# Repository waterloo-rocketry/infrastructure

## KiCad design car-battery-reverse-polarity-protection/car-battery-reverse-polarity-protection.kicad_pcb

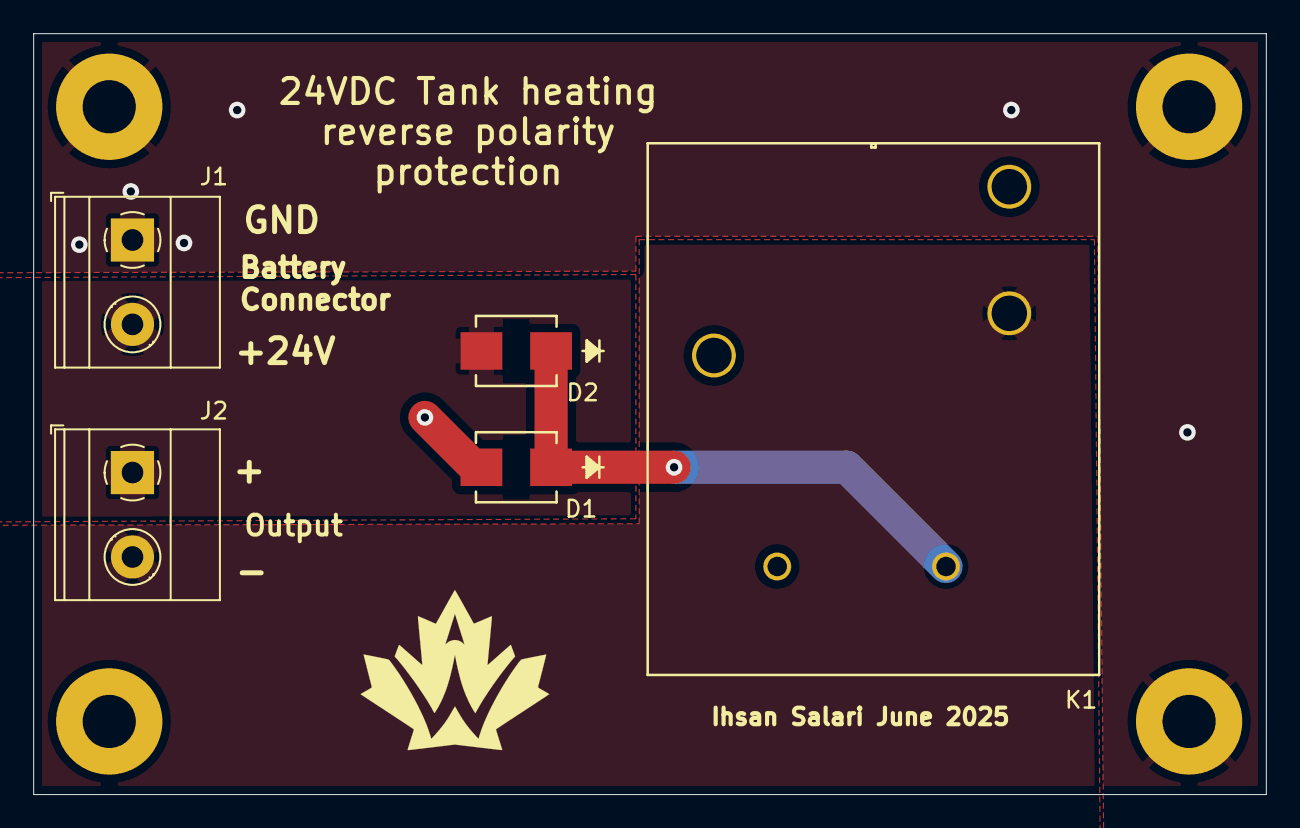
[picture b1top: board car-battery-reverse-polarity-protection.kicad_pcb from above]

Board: 2 copper layers, 74.2 x 45.8 mm, 10 parts (1 on the bottom side), 4 nets.

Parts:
D1, D2: STPS2L25U; SMB_STM-M
H1, H2, H3, H5: MountingHole_Pad; MountingHole_3.2mm_M3_Pad
H4: Logo; rocketry_logo_small_noletters
J1: Battery Connector; TerminalBlock_Phoenix_MKDS-1,5-2-5.08_1x02_P5.08mm_Horizont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
J2: Output; TerminalBlock_Phoenix_MKDS-1,5-2-5.08_1x02_P5.08mm_Horizont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
K1: AZ2150-1AE-24DEF; AZ2150_AMZ

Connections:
+BATT: D2.2 (A), J1.2, J2.1
/relay_coil: D1.1 (K), D2.1 (K), K1.A1
/relay_load_terminal: J2.2, K1.14
GND: D1.2 (A), H1.1, H2.1, H3.1, H5.1, J1.1, K1.13, K1.A2

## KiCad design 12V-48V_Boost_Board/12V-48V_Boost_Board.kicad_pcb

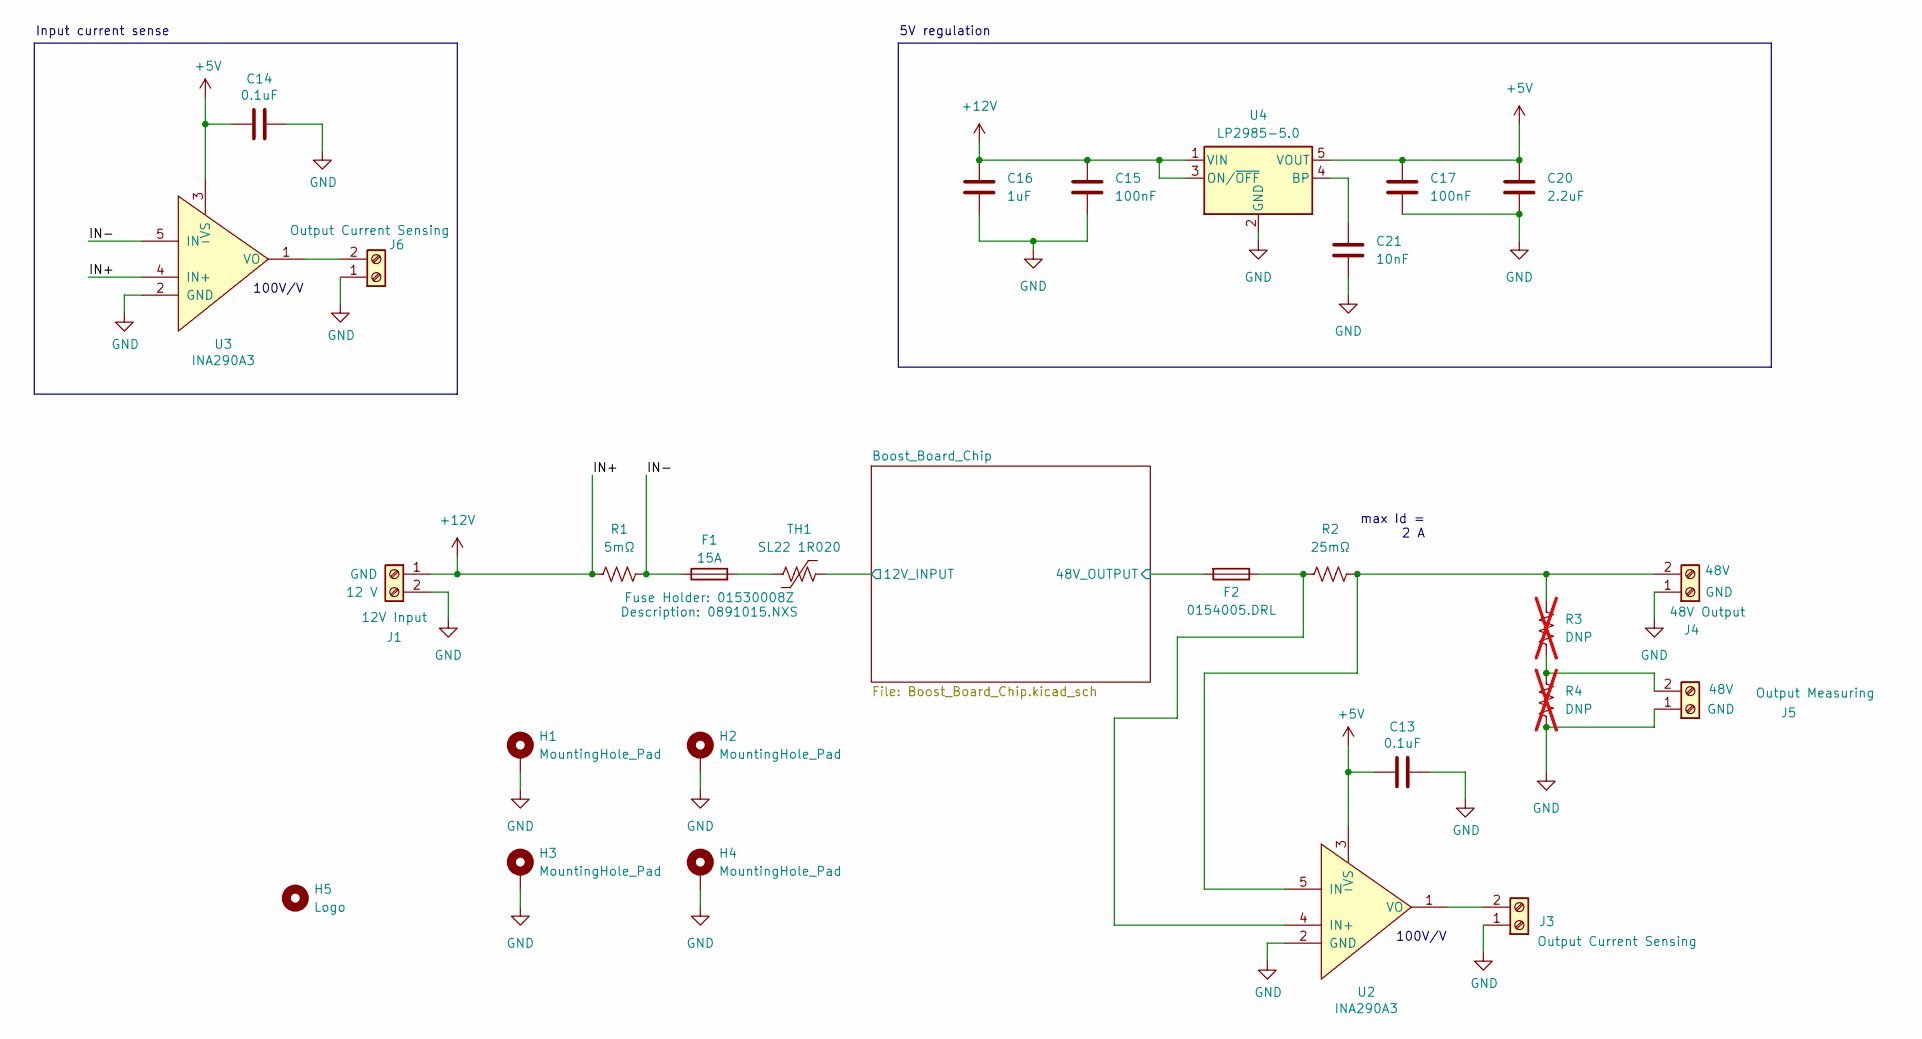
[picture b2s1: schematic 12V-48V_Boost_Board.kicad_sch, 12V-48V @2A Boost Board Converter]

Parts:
C13, C14: 0.1uF; C_0805_2012Metric_Pad1.18x1.45mm_HandSolder
C15, C17: 100nF; C_0805_2012Metric_Pad1.18x1.45mm_HandSolder
C16: 1uF; C_0805_2012Metric_Pad1.18x1.45mm_HandSolder
C20: 2.2uF; C_0805_2012Metric_Pad1.18x1.45mm_HandSolder
C21: 10nF; C_0805_2012Metric_Pad1.18x1.45mm_HandSolder
F1: 15A; 01530009Z
F2: 0154005.DRL; 0154Series_LTF
H1, H2, H3, H4: MountingHole_Pad; MountingHole_3.2mm_M3_Pad
H5: Logo; Logo_SilkScreen_10mm
J1: 12V Input; TerminalBlock_Phoenix_PT-1,5-2-5.0-H_1x02_P5.00mm_Horizontal
J3, J6: Output Current Sensing; TerminalBlock_Phoenix_PT-1,5-2-5.0-H_1x02_P5.00mm_Horizontal
J4: 48V Output; TerminalBlock_Phoenix_PT-1,5-2-5.0-H_1x02_P5.00mm_Horizontal
J5: Output Measuring; TerminalBlock_Phoenix_PT-1,5-2-5.0-H_1x02_P5.00mm_Horizontal
R1: 5mΩ; R_2816_7142Metric_Pad3.20x4.45mm_HandSolder
R2: 25mΩ; R_0805_2012Metric_Pad1.20x1.40mm_HandSolder
R3, R4: DNP; R_0805_2012Metric_Pad1.20x1.40mm_HandSolder; not fitted
TH1: 20A; Inrush Current Limiter
U2, U3: INA290A3; SC70-5_DCK_TEX
U4: LP2985-5.0; SOT-23-5

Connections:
+5V: C13.2, C14.2, C17.1, C20.1, U2.3 (VS), U3.3 (VS), U4.5 (VOUT)
+12V: C15.1, C16.1, J1.1, R1.1, U3.4 (IN+), U4.1 (VIN), U4.3 (ON/~OFF)
/Boost_Board_Chip/12V_INPUT: TH1.2; also elsewhere on the board
/Boost_Board_Chip/48V_OUTPUT: F2.2; also elsewhere on the board
/IN-: F1.1, R1.2, U3.5 (IN-)
GND: C13.1, C14.1, C15.2, C16.2, C17.2, C20.2, C21.2, H1.1, H2.1, H3.1, H4.1, J1.2, J3.1, J4.1, J5.1, J6.1, R4.1, U2.2 (GND), U3.2 (GND), U4.2 (GND); also elsewhere on the board
unnamed: F1.2, TH1.1
unnamed: J3.2, U2.1 (VO)
unnamed: J4.2, R2.2, R3.2, U2.5 (IN-)
unnamed: J5.2, R3.1, R4.2
unnamed: J6.2, U3.1 (VO)
unnamed: F2.1, R2.1, U2.4 (IN+)
unnamed: C21.1, U4.4 (BP)

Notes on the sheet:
max Id = 2 A
100V/V
5V regulation
Input current sense

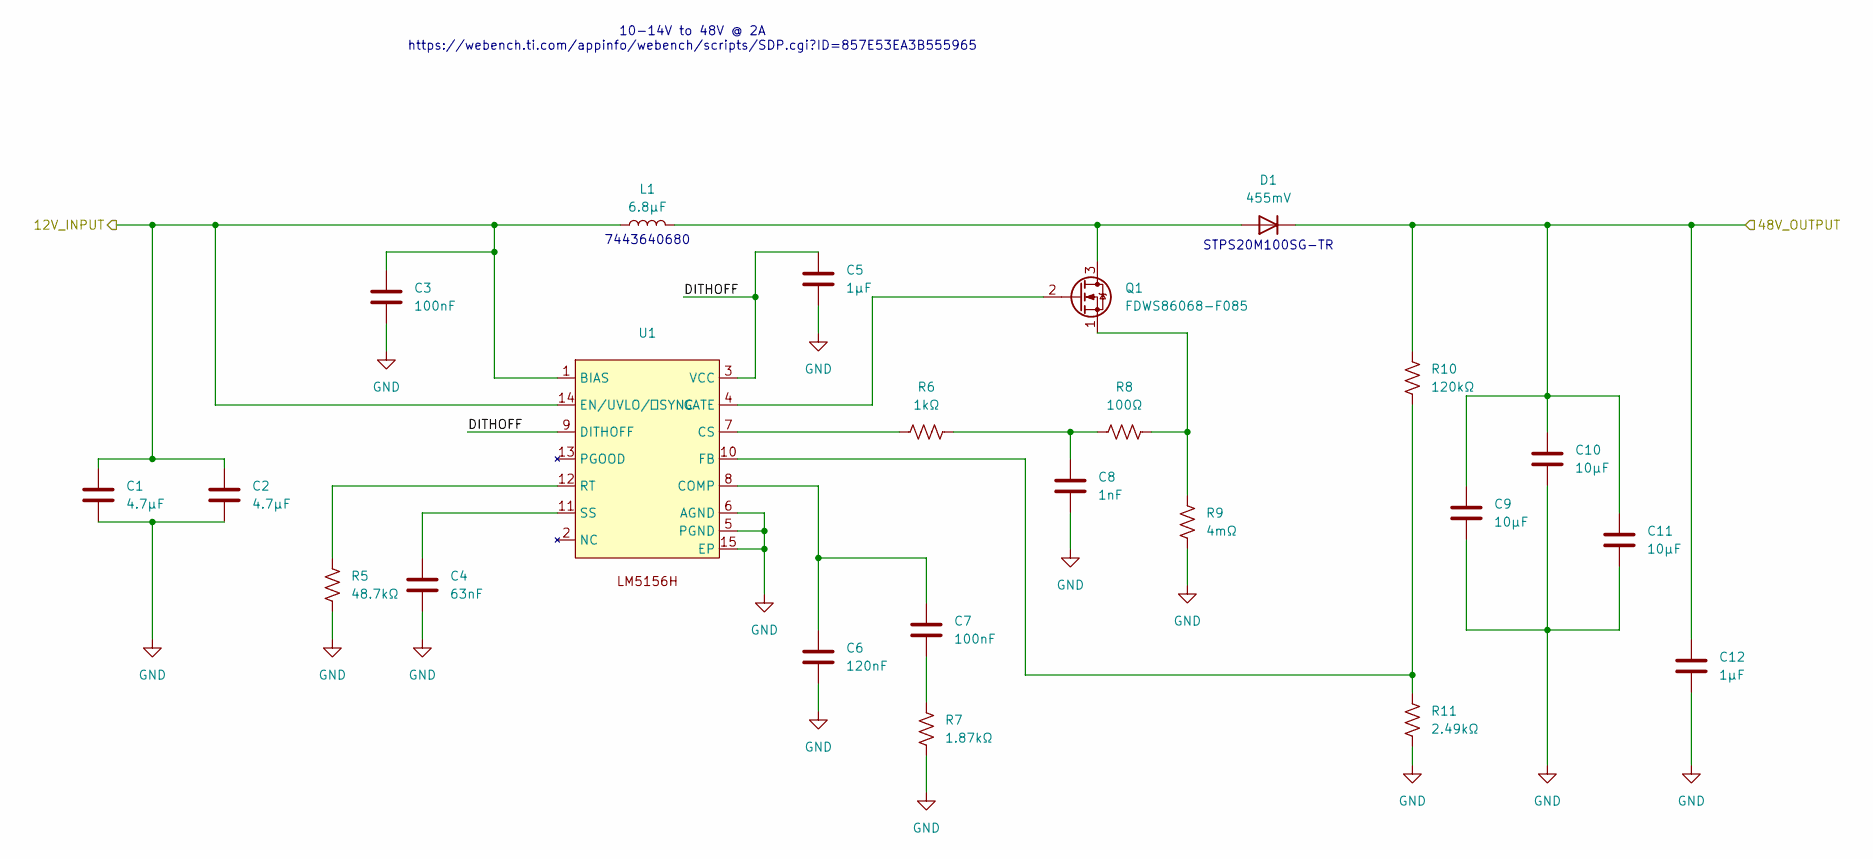
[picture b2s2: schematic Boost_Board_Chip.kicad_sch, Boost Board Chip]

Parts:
C1, C2: 4.7µF; GRM31CR71H475KA12L
C3, C7: 100nF; C_0805_2012Metric_Pad1.18x1.45mm_HandSolder
C4: 63nF; C_1206_3216Metric_Pad1.33x1.80mm_HandSolder
C5: 1µF; C_0805_2012Metric_Pad1.18x1.45mm_HandSolder
C6: 120nF; C_0805_2012Metric_Pad1.18x1.45mm_HandSolder
C8: 1nF; C_0805_2012Metric_Pad1.18x1.45mm_HandSolder
C9, C10, C11: 10µF; CAPC6050X550N
C12: 1µF; CAPC3216X180N
D1: 455mV; D2PAK_STM-M
L1: 6.8µF; WE-HCF_SMD_HIGH-CURRENT_INDUCTOR
Q1: FDWS86068-F085; Q1 Mosfet
R5: 48.7kΩ; R_0805_2012Metric_Pad1.20x1.40mm_HandSolder
R6: 1kΩ; R_0805_2012Metric_Pad1.20x1.40mm_HandSolder
R7: 1.87kΩ; R_0805_2012Metric_Pad1.20x1.40mm_HandSolder
R8: 100Ω; R_0805_2012Metric_Pad1.20x1.40mm_HandSolder
R9: 4mΩ; RES_WSL25124L000FEB
R10: 120kΩ; R_0805_2012Metric_Pad1.20x1.40mm_HandSolder
R11: 2.49kΩ; R_0805_2012Metric_Pad1.20x1.40mm_HandSolder
U1: LM5156H

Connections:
/Boost_Board_Chip/12V_INPUT: C1.1, C2.1, C3.1, L1.1, U1.1 (BIAS), U1.14 (EN/UVLO/ SYNC); also elsewhere on the board
/Boost_Board_Chip/48V_OUTPUT: C9.1, C10.1, C11.1, C12.1, D1.3 (K), R10.1; also elsewhere on the board
/Boost_Board_Chip/DITHOFF: C5.1, U1.3 (VCC), U1.9 (DITHOFF)
GND: C1.2, C2.2, C3.2, C4.2, C5.2, C6.2, C8.2, C9.2, C10.2, C11.2, C12.2, R5.2, R7.2, R9.2, R11.2, U1.5 (PGND), U1.6 (AGND), U1.15 (EP); also elsewhere on the board
unnamed: C7.2, R7.1
unnamed: C8.1, R6.2, R8.1
unnamed: D1.1 (A), L1.2, Q1.3 (D)
unnamed: Q1.2 (G), U1.4 (GATE)
unnamed: Q1.1 (S), R8.2, R9.1
unnamed: C6.1, C7.1, U1.8 (COMP)
unnamed: R6.1, U1.7 (CS)
unnamed: R10.2, R11.1, U1.10 (FB)
unnamed: R5.1, U1.12 (RT)
unnamed: C4.1, U1.11 (SS)

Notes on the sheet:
STPS20M100SG-TR
7443640680
10-14V to 48V @ 2A https://webench.ti.com/appinfo/webench/scripts/SDP.cgi?ID=857E53EA3B555965

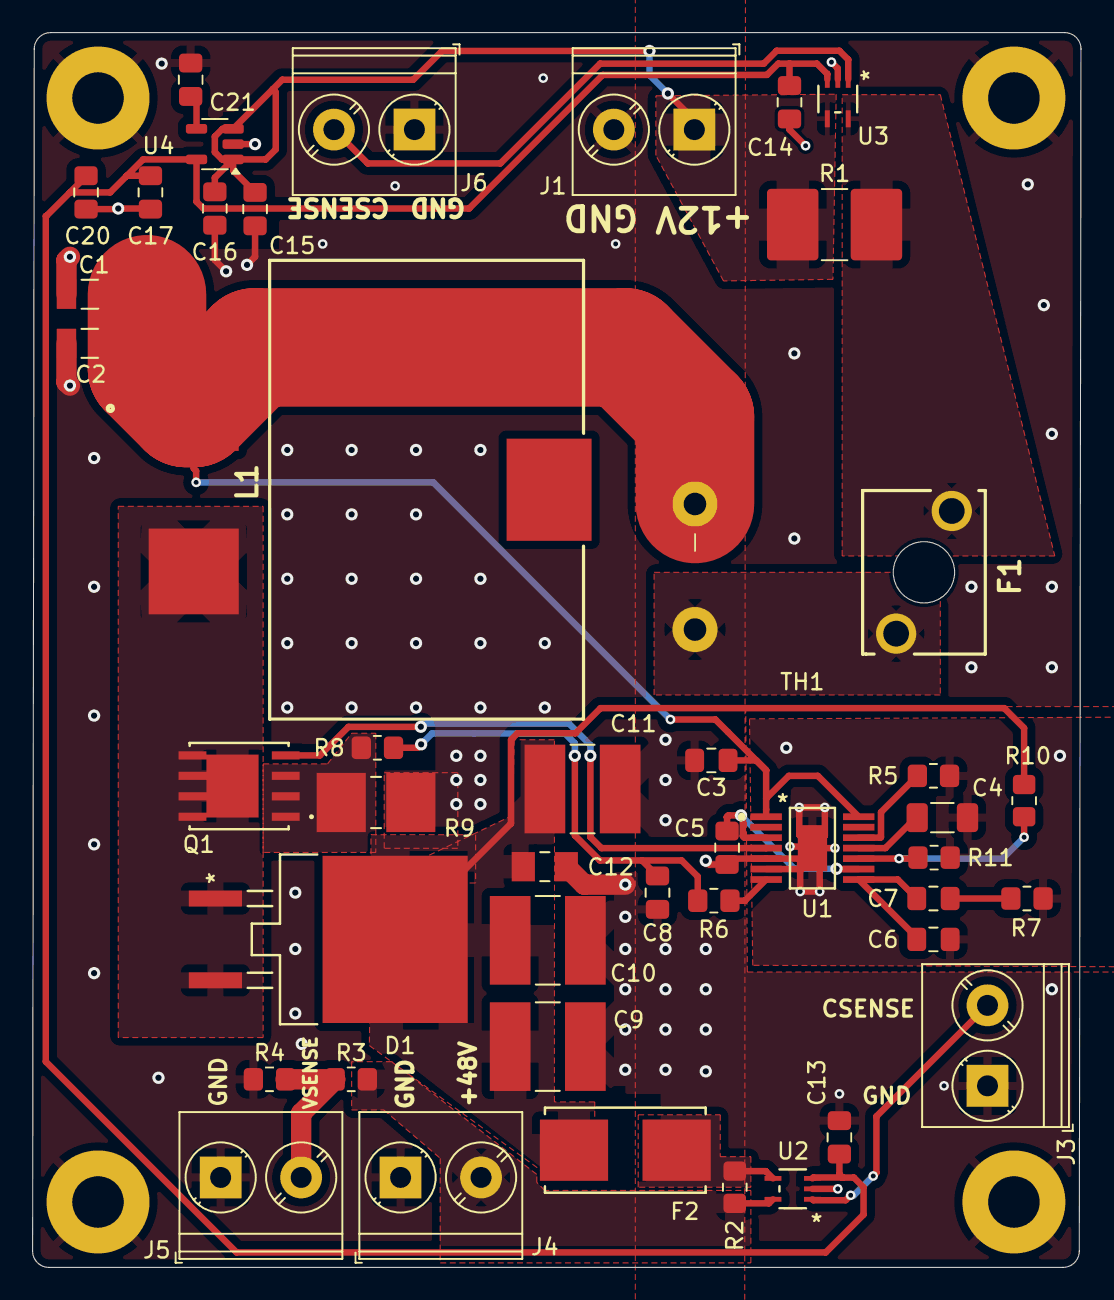
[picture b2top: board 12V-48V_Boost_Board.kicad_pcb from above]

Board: 2 copper layers, 65.1 x 76.7 mm, 50 parts (1 on the bottom side), 24 nets.

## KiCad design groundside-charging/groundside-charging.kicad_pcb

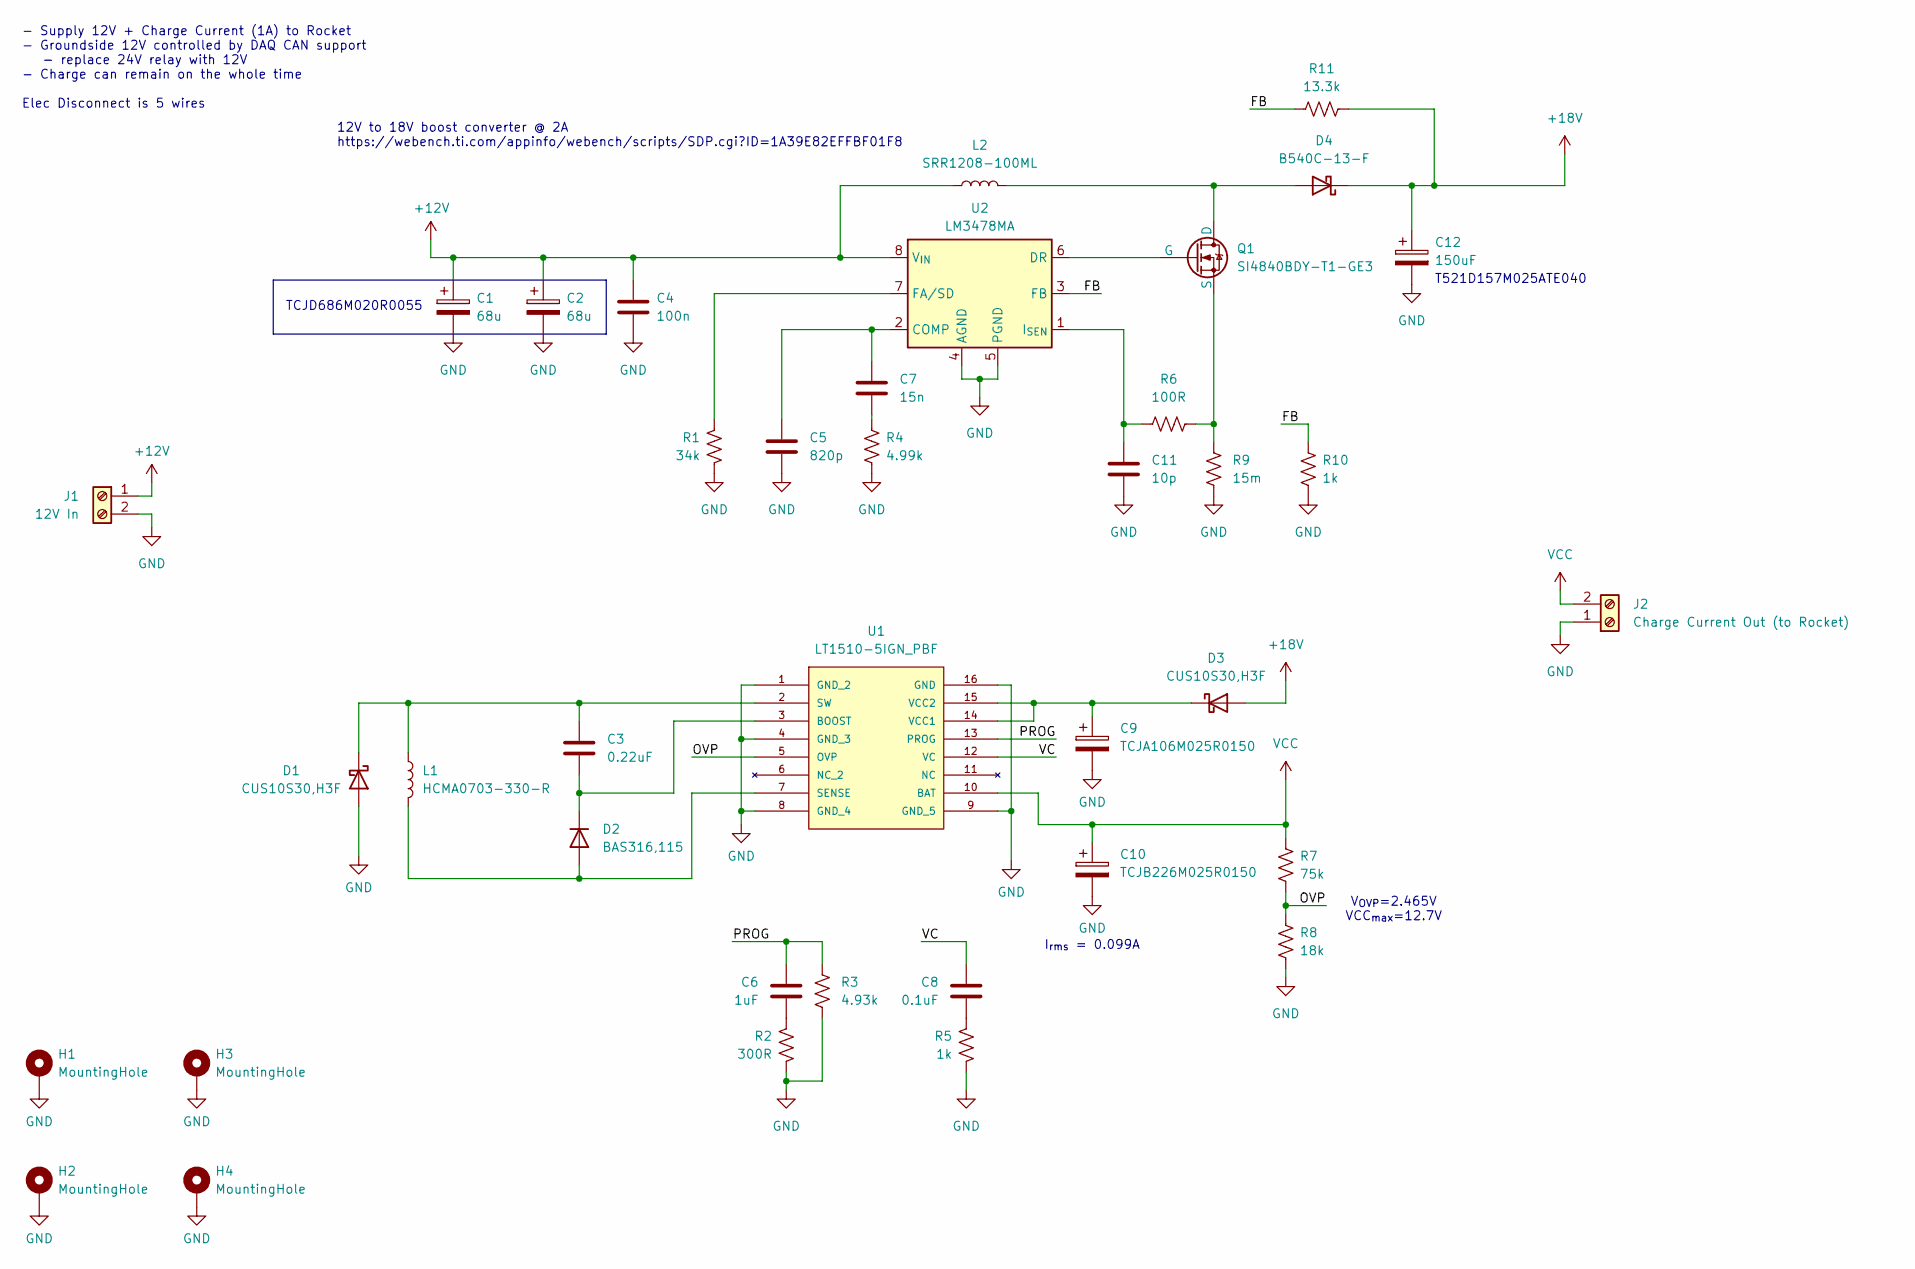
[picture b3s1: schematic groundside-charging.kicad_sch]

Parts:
C1, C2: 68u; CP_EIA-7343-31_Kemet-D_Pad2.25x2.55mm_HandSolder
C3: 0.22uF; C_0805_2012Metric_Pad1.18x1.45mm_HandSolder
C4: 100n; C_0805_2012Metric_Pad1.18x1.45mm_HandSolder
C5: 820p; C_0805_2012Metric_Pad1.18x1.45mm_HandSolder
C6: 1uF; C_0805_2012Metric_Pad1.18x1.45mm_HandSolder
C7: 15n; C_0805_2012Metric_Pad1.18x1.45mm_HandSolder
C8: 0.1uF; C_0805_2012Metric_Pad1.18x1.45mm_HandSolder
C9: TCJA106M025R0150; CAPPM3216X180N
C10: TCJB226M025R0150; CAPPM7343X310N
C11: 10p; C_0805_2012Metric_Pad1.18x1.45mm_HandSolder
C12: 150uF; CP_EIA-7343-31_Kemet-D_Pad2.25x2.55mm_HandSolder
D1, D3: CUS10S30,H3F; D_SOD-323_HandSoldering
D2: BAS316,115; D_SOD-323_HandSoldering
D4: B540C-13-F; D_SMC
H1, H2, H3, H4: MountingHole; MountingHole_3.2mm_M3_Pad_Via
J1: 12V In; TerminalBlock_Phoenix_PT-1,5-2-5.0-H_1x02_P5.00mm_Horizontal
J2: Charge Current Out (to Rocket); TerminalBlock_Phoenix_PT-1,5-2-5.0-H_1x02_P5.00mm_Horizontal
L1: HCMA0703-330-R
L2: SRR1208-100ML; IND_BOURNS_SRR1208
Q1: SI4840BDY-T1-GE3
R1: 34k; R_0805_2012Metric_Pad1.20x1.40mm_HandSolder
R2: 300R; R_0805_2012Metric_Pad1.20x1.40mm_HandSolder
R3: 4.93k; R_0805_2012Metric_Pad1.20x1.40mm_HandSolder
R4: 4.99k; R_0805_2012Metric_Pad1.20x1.40mm_HandSolder
R5, R10: 1k; R_0805_2012Metric_Pad1.20x1.40mm_HandSolder
R6: 100R; R_0805_2012Metric_Pad1.20x1.40mm_HandSolder
R7: 75k; R_0805_2012Metric_Pad1.20x1.40mm_HandSolder
R8: 18k; R_0805_2012Metric_Pad1.20x1.40mm_HandSolder
R9: 15m; R_0805_2012Metric_Pad1.20x1.40mm_HandSolder
R11: 13.3k; R_0805_2012Metric_Pad1.20x1.40mm_HandSolder
U1: LT1510-5IGN_PBF; SSOP-16_GN; MANUFACTURER_PART_NUMBER lt15105ign
U2: LM3478MA; SOIC-8_3.9x4.9mm_P1.27mm

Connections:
+12V: C1.1, C2.1, C4.1, J1.1, L2.1, U2.8 (V_{IN})
+18V: C12.1, D3.2 (A), D4.1 (K), R11.2
/FB: R10.1, R11.1, U2.3 (FB)
/OVP: R7.2, R8.1, U1.5 (OVP)
/PROG: C6.1, R3.1, U1.13 (PROG)
/VC: C8.1, U1.12 (VC)
GND: C1.2, C2.2, C4.2, C5.2, C9.2, C10.2, C11.2, C12.2, D1.2 (A), H1.1, H2.1, H3.1, H4.1, J1.2, J2.1, R1.2, R2.2, R3.2, R4.2, R5.2, R8.2, R9.1, R10.2, U1.1 (GND_2), U1.4 (GND_3), U1.8 (GND_4), U1.9 (GND_5), U1.16 (GND), U2.4 (AGND), U2.5 (PGND)
unnamed: C6.2, R2.1
unnamed: C7.2, R4.1
unnamed: C8.2, R5.1
unnamed: C3.1, D1.1 (K), L1.1, U1.2 (SW)
unnamed: D2.2 (A), L1.2, U1.7 (SENSE)
unnamed: C3.2, D2.1 (K), U1.3 (BOOST)
unnamed: C9.1, D3.1 (K), U1.14 (VCC1), U1.15 (VCC2)
unnamed: D4.2 (A), L2.2, Q1.1 (D)
unnamed: Q1.2 (G), U2.6 (DR)
unnamed: Q1.3 (S), R6.2, R9.2
unnamed: C5.1, C7.1, U2.2 (COMP)
unnamed: R1.1, U2.7 (FA/SD)
unnamed: C11.1, R6.1, U2.1 (I_{SEN})
VCC: C10.1, J2.2, R7.1, U1.10 (BAT)

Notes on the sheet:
TCJD686M020R0055
T521D157M025ATE040
12V to 18V boost converter @ 2A https://webench.ti.com/appinfo/webench/scripts/SDP.cgi?ID=1A39E82EFFBF01F8
V_{OVP}=2.465V VCC_{max}=12.7V
- Supply 12V + Charge Current (1A) to Rocket - Groundside 12V controlled by DAQ CAN support - replace 24V relay with 12V - Charge can remain on the whole time Elec Disconnect is 5 wires
I_{rms} = 0.099A

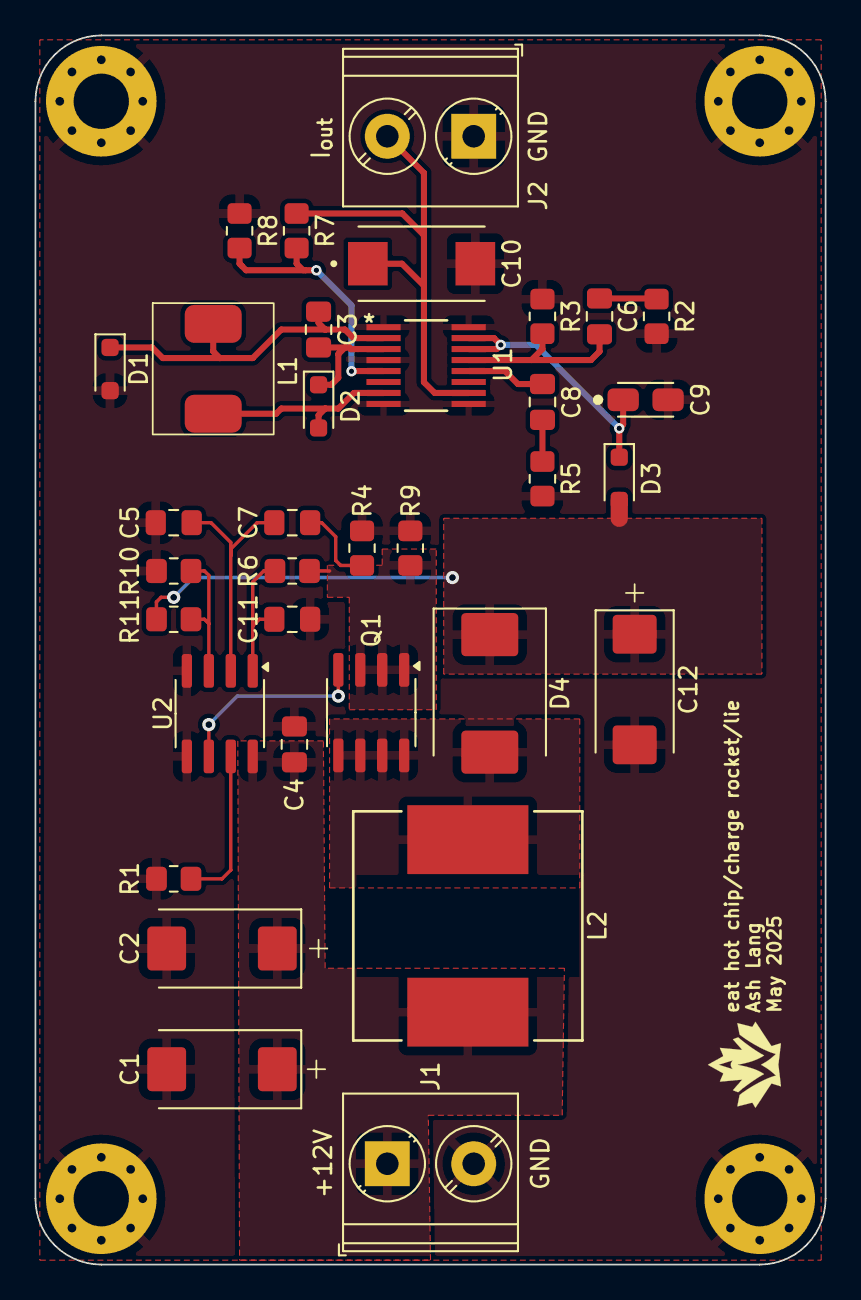
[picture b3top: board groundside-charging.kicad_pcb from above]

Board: 2 copper layers, 45.7 x 71.1 mm, 38 parts (0 on the bottom side), 21 nets.

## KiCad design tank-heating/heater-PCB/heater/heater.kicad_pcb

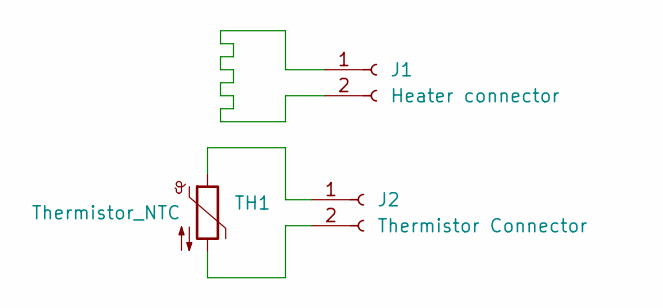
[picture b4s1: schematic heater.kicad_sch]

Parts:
J1: Heater connector; XT30_pads
J2: Thermistor Connector; GCT_BG300-02-X-X-A_REVC
TH1: Thermistor_NTC; R_0805_2012Metric_Pad1.20x1.40mm_HandSolder

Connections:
unnamed: J1.1, J1.2
unnamed: J2.1, TH1.1
unnamed: J2.2, TH1.2

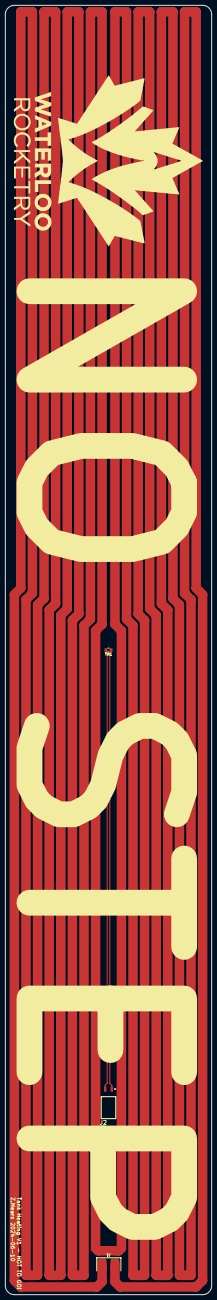
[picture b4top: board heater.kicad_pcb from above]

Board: 2 copper layers, 80.0 x 500.0 mm, 3 parts (0 on the bottom side), 3 nets.

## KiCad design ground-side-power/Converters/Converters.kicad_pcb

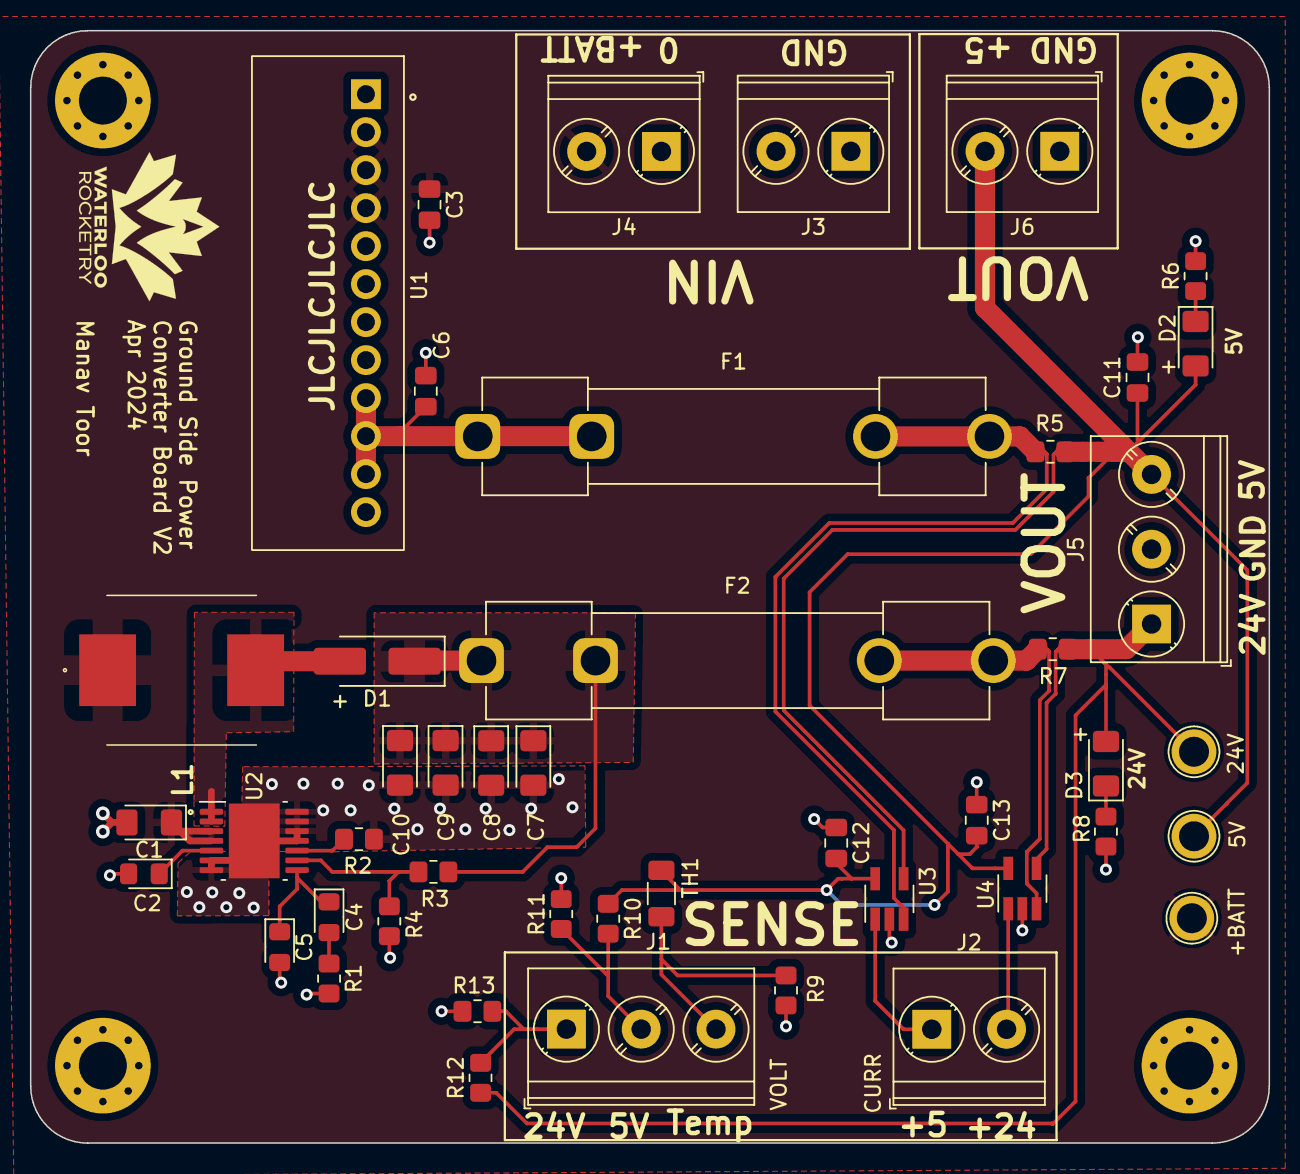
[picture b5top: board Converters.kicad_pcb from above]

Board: 2 copper layers, 82.8 x 74.4 mm, 46 parts (0 on the bottom side), 21 nets.

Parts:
5V, 24V: TestPoint; TestPoint_Plated_Hole_D2.0mm
+BATT: TestPoint; TestPoint_Plated_Hole_D2.0mm
C1: 10uF; D_1206_3216Metric_Pad1.42x1.75mm_HandSolder
C2: 0.047uF; D_0805_2012Metric_Pad1.15x1.40mm_HandSolder
C3, C11: 10uF; C_0805_2012Metric_Pad1.18x1.45mm_HandSolder
C4: 100nF; D_0805_2012Metric_Pad1.15x1.40mm_HandSolder
C5: 1300pF; D_0805_2012Metric_Pad1.15x1.40mm_HandSolder
C6: 22uF; C_0805_2012Metric_Pad1.18x1.45mm_HandSolder
C7, C8, C9, C10: 6.8uF; D_1206_3216Metric_Pad1.42x1.75mm_HandSolder
C12, C13: 0.1u; C_0805_2012Metric_Pad1.18x1.45mm_HandSolder
D1: SK54A-LTP; D_SMA_Handsoldering
D2, D3: LED; LED_1206_3216Metric_Pad1.42x1.75mm_HandSolder
F1: 3A Fuse; Fuseholder_Clip-6.3x32mm_Littelfuse_102_122_Inline_P34.21x7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
F2: 3A; Fuseholder_Clip-6.3x32mm_Littelfuse_102_122_Inline_P34.21x7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
J1: DAQ Voltage Sensing; TerminalBlock_Phoenix_PT-1,5-3-5.0-H_1x03_P5.00mm_Horizontal
J2: DAQ Current Sensing; TerminalBlock_Phoenix_PT-1,5-2-5.0-H_1x02_P5.00mm_Horizontal
J3: Ground Connections; TerminalBlock_Phoenix_PT-1,5-2-5.0-H_1x02_P5.00mm_Horizontal
J4: BATT_IN; TerminalBlock_Phoenix_PT-1,5-2-5.0-H_1x02_P5.00mm_Horizontal
J5: POWER_OUT; TerminalBlock_Phoenix_PT-1,5-3-5.0-H_1x03_P5.00mm_Horizontal
J6: 5V_IN; TerminalBlock_Phoenix_PT-1,5-2-5.0-H_1x02_P5.00mm_Horizontal
L1: ETQ-P5M100YFC; ETQP5M_YFC_YGC
R1: 2k; R_0805_2012Metric_Pad1.20x1.40mm_HandSolder
R2: 78.7k; R_0805_2012Metric_Pad1.20x1.40mm_HandSolder
R3: 187k; R_0805_2012Metric_Pad1.20x1.40mm_HandSolder
R4, R9: 10k; R_0805_2012Metric_Pad1.20x1.40mm_HandSolder
R5: 0.01R; R_0805_2012Metric_Pad1.20x1.40mm_HandSolder
R6: 270R; R_0805_2012Metric_Pad1.20x1.40mm_HandSolder
R7: 16mR; R_0805_2012Metric_Pad1.20x1.40mm_HandSolder
R8: 1.2k; R_0805_2012Metric_Pad1.20x1.40mm_HandSolder
R10: 47k; R_0805_2012Metric_Pad1.20x1.40mm_HandSolder
R11, R13: 100k; R_0805_2012Metric_Pad1.20x1.40mm_HandSolder
R12: 660k; R_0805_2012Metric_Pad1.20x1.40mm_HandSolder
TH1: B57621C5103K062; R_1206_3216Metric_Pad1.30x1.75mm_HandSolder
U1: K7805-3AR3
U2: TPS55340; HTSSOP-14-1EP_4.4x5mm_P0.65mm_EP3.4x5mm_Mask3x3.1mm
U3, U4: INA180; SOT-23-5_HandSoldering

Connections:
+5V: 5V.1, C11.1, C12.2, C13.2, D2.2 (A), J5.3, J6.2, R5.2, R10.1, TH1.1, U3.4 (IN-), U3.5 (VS), U4.5 (VS)
+24V: 24V.1, D3.2 (A), J5.1, R7.2, R12.1, U4.4 (IN-)
+BATT: +BATT.1, C1.1, C3.1, J4.2, L1.1, U1.2 (VIN), U1.3 (VIN), U1.4 (VIN), U2.3 (VIN), U2.4 (EN)
/5V_OUT: J2.1, U3.1 (VO)
/5V_Sense+: F1.2, R5.1, U3.3 (IN+)
/5V_VOLTAGE: J1.2, R10.2, R11.1
/24V_OUT: J2.2, U4.1 (VO)
/24V_Sense+: F2.2, R7.1, U4.3 (IN+)
/24V_VOLTAGE: J1.1, R12.2, R13.1
/Temp: J1.3, R9.1, TH1.2
GND: C1.2, C2.2, C3.2, C5.2, C6.2, C7.2, C8.2, C9.2, C10.2, C11.2, C12.1, C13.1, J3.1, J3.2, J4.1, J5.2, J6.1, R1.2, R2.2, R4.2, R6.2, R8.2, R9.2, R11.2, R13.2, U1.5 (GND), U1.6 (GND), U1.7 (GND), U1.8 (GND), U2.6 (SYNC), U2.7 (AGND), U2.11 (NC), U2.12 (PGND), U2.13 (PGND), U2.14 (PGND), U3.2 (GND), U4.2 (GND)
unnamed: C4.2, R1.1
unnamed: D1.2 (A), L1.2, U2.1 (SW), U2.2 (SW)
unnamed: C7.1, C8.1, C9.1, C10.1, D1.1 (K), F2.1, R3.2
unnamed: D2.1 (K), R6.1
unnamed: D3.1 (K), R8.1
unnamed: C6.1, F1.1, U1.9 (+VO1), U1.10 (+VO1), U1.11 (+VO2)
unnamed: C4.1, C5.1, U2.8 (COMP)
unnamed: R3.1, R4.1, U2.9 (FB)
unnamed: R2.1, U2.10 (FREQ)
unnamed: C2.1, U2.5 (SS)

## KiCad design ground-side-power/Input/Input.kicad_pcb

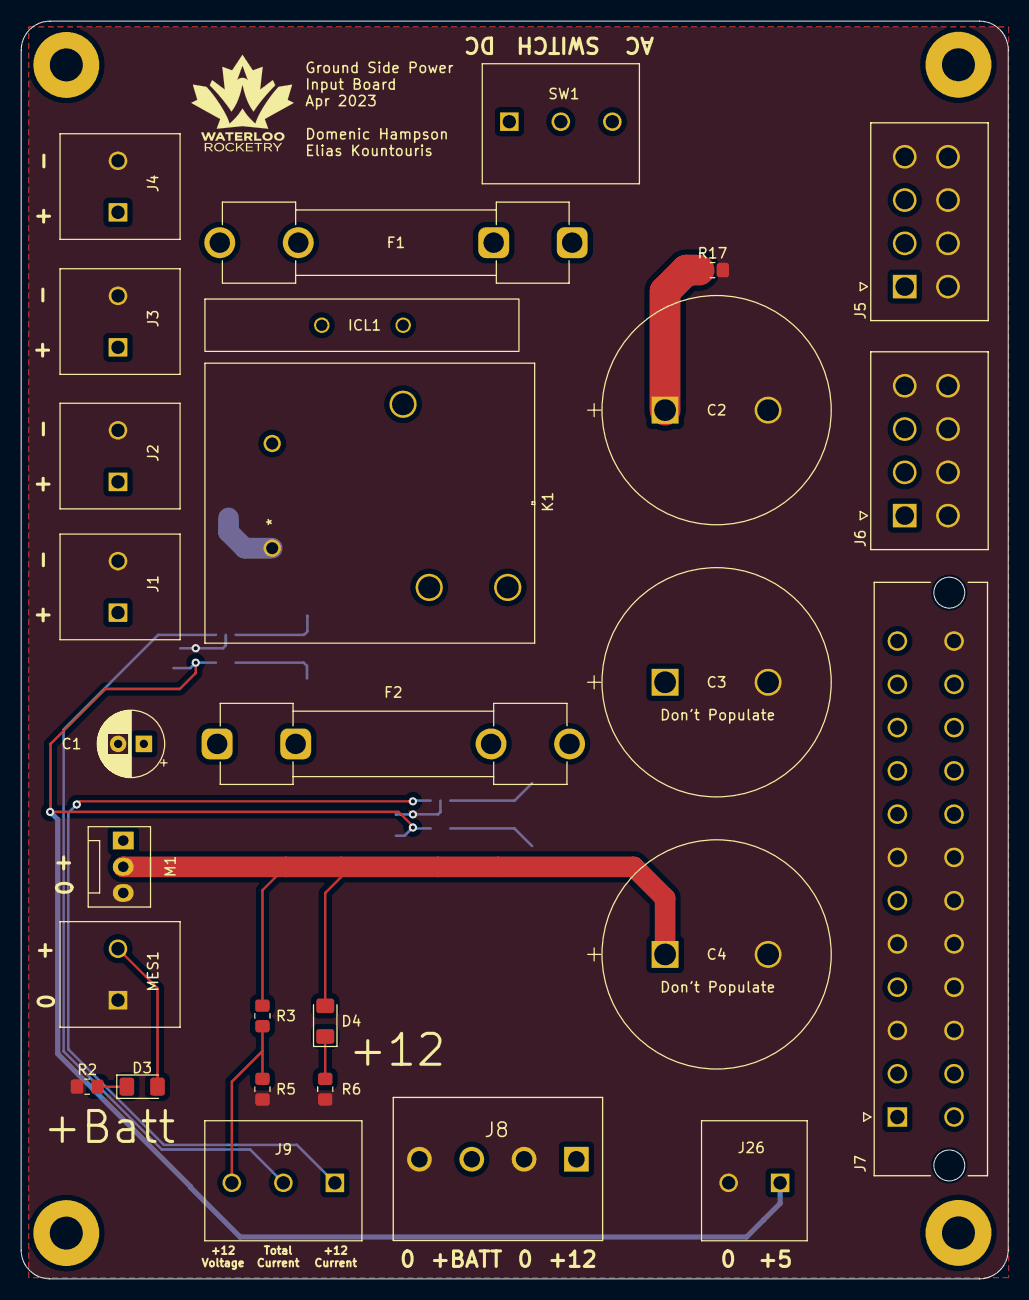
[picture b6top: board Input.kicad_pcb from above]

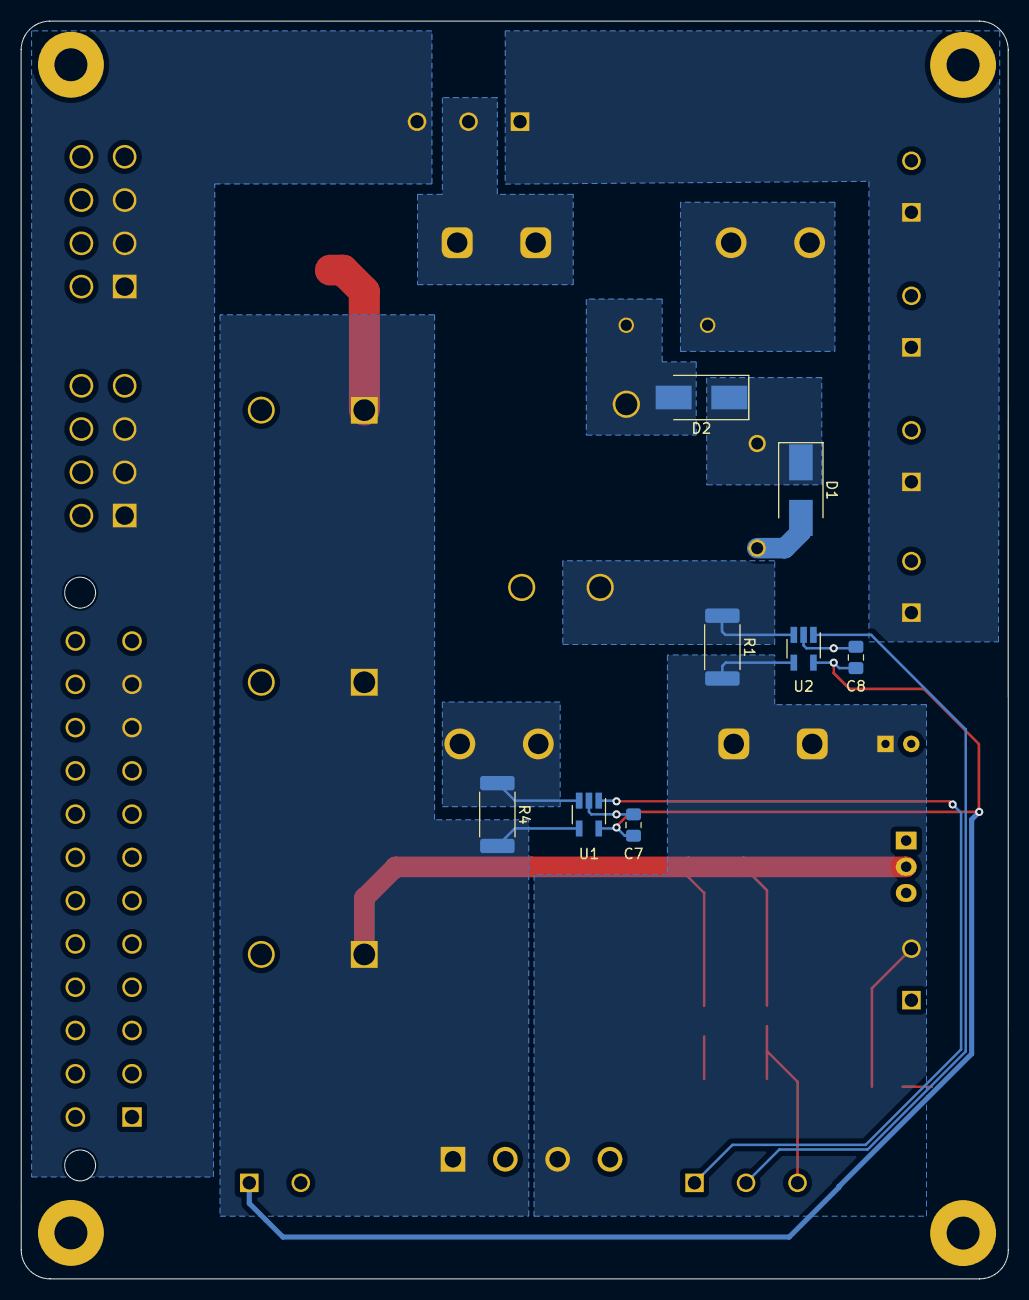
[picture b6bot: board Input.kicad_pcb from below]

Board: 2 copper layers, 95.8 x 122.1 mm, 36 parts (8 on the bottom side), 17 nets.

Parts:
C1: 100uF; CP_Radial_D6.3mm_P2.50mm
C2, C3, C4: 22mF; LLS1C223MELZ
C7, C8: 0.1u; C_0805_2012Metric_Pad1.18x1.45mm_HandSolder
D1, D2: 10BQ015; D_SMB_Handsoldering
D3, D4: LED_Small; D_1206_3216Metric_Pad1.42x1.75mm_HandSolder
F1, F2: 25A Fuse; Fuseholder_Clip-6.3x32mm_Littelfuse_102_122_Inline_P34.21x7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
ICL1: SL32 2R025-B
J1, J2, J3, J4: Battery Terminals; 1935310
J5, J6: 874270842; MOLEX_874270842
J7: ATX-24; MOLEX_442060001
J8: Conn_01x03_Female; CUI_TB008A-508-04BE
J9: Conn_01x03_Female; 1935323
J26: Conn_01x02_Female; 1935310
K1: AZ2150-1A-12DEF
M1: Fan_PC_Chassis; FanPinHeader_1x03_P2.54mm_Vertical
MES1: PRT-14313; 1935310
R1, R4: 0.0015; R_2512_6332Metric_Pad1.40x3.35mm_HandSolder
R2, R6: R_Small_US; R_0805_2012Metric_Pad1.20x1.40mm_HandSolder
R3: 220K; R_0805_2012Metric_Pad1.20x1.40mm_HandSolder
R5: 100K; R_0805_2012Metric_Pad1.20x1.40mm_HandSolder
R17: 10k; R_0805_2012Metric_Pad1.20x1.40mm_HandSolder
SW1: GRB234A2NABA1; 1935323
U1, U2: INA180; SOT-23-5_HandSoldering

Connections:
+5V: C7.2, C8.2, J26.1, U1.5 (VS), U2.5 (VS)
+12V: C2.1, C3.1, C4.1, D4.2 (A), J8.1, M1.2 (+), R3.1, R4.2, R17.1, U1.4 (IN-)
+BATT: C1.1, D3.2 (A), F2.1, J8.3, MES1.2 (+), R1.2, U2.4 (IN-)
/12V_OUT: J9.1, U1.1 (VO)
/12V_Sense+: F2.2, R4.1, U1.3 (IN+)
/12_VOLTAGE: J9.3, R3.2, R5.1
/ACPowerSupply: J5.1, J5.2, J5.3, J6.1, J6.2, J6.3, J7.10 (+12V), J7.11 (+12V), SW1.3 (C)
/BatteryPowerSupply: J1.1, J2.1, J3.1, J4.1, SW1.1 (A)
/Sys_Sense+: K1.2, R1.1, U2.3 (IN+)
/TOTAL_OUT: J9.2, U2.1 (VO)
GND: C1.2, C2.2, C3.2, C4.2, C7.1, C8.1, D1.2 (A), J1.2, J2.2, J3.2, J4.2, J5.4, J5.5, J5.6, J5.7, J5.8, J6.4, J6.5, J6.6, J6.7, J6.8, J7.3 (GND), J7.5 (GND), J7.7 (GND), J7.15 (GND), J7.16 (PS_ON#), J7.17 (GND), J7.18 (GND), J7.19 (GND), J7.24 (GND), J8.2, J8.4, J26.2, K1.1, M1.3 (-), MES1.1 (-), R2.1, R5.2, R6.1, R17.2, U1.2 (GND), U2.2 (GND)
unnamed: D1.1 (K), D2.1 (K), K1.5
unnamed: D2.2 (A), ICL1.2, K1.4
unnamed: D3.1 (K), R2.2
unnamed: D4.1 (K), R6.2
unnamed: F1.1, SW1.2 (B)
unnamed: F1.2, ICL1.1
